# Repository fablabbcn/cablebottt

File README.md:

# CABLEBOTTT

**A hands-on STEAM workshop by FLU @ Fab Lab Barcelona.**

Design, fabricate and program a **cable-driven robot** (cablebot). Participants build a small robot that travels along a cable using a rotating motor, and bring it to life by wiring up inputs (light, distance) and outputs (motor, LED, buzzer, servo). The activity combines **mechanics + digital fabrication + computational thinking** in an accessible, creative format.

> Based on a yellow gearmotor driven from a **Seeed Studio XIAO ESP32-C3**, on a custom PCB.

---

## What you'll build

The cablebot comes in **two behaviors**, using the same hardware:

| | **Sketch A — autonomous** | **Sketch B — teleoperated** |
|---|---|---|
| **Idea** | The robot decides for itself | You drive it from your phone |
| **How** | Follows light using 2 LDR sensors | Serves a webapp over its own WiFi |
| **Inputs** | 2 light sensors (LDR) | Distance sensor (optional) |
| **Outputs** | Motor | Motor, color LED, buzzer, servo |
| **Libraries** | None | Adafruit NeoPixel + VL53L1X |
| **Best for** | Seeing a closed feedback loop | Programming your own behaviors |

Both are fully documented — see **[Programming](#3-programming)** below.

---

## Folder structure

```
cablebottt/
├── README.md                        ← you are here (project index)
│
├── fabrication/                     ← everything you cut / print / mill
│   ├── ⟨laser_pieces.svg⟩           ← laser-cut structure (the 3 assembly pieces)
│   ├── ⟨mount_3d.stl⟩               ← 3D-printed parts (if any)
│   ├── pcb/                         ← custom PCB (KiCad project + Gerbers)
│   │   ├── fab26_cablebot.kicad_pro
│   │   ├── fab26_cablebot.kicad_sch
│   │   ├── fab26_cablebot.kicad_pcb
│   │   ├── gerber/                  ← ready-to-mill / ready-to-order
│   │   └── svg/fab26_cablebot-preview.svg
│   └── silkscreen/back_silkscreen.svg
│
├── code/
│   ├── cablebottt_laser/cablebottt.ino        ← Sketch A (autonomous)
│   └── cablebottt_web/cablebottt_web.ino      ← Sketch B (teleoperated)
│
├── docs/
│   ├── cablebottt_sketch_A_tutorial.md        ← how to program Sketch A
│   └── cablebottt_sketch_B_tutorial.md        ← how to program Sketch B
│
└── images/                          ← photos & reference
    ├── ⟨assembled_bot.jpg⟩
    ├── ⟨soldering_xiao.jpg⟩
    └── ⟨pcb_render.png⟩
```

> **⟨…⟩ = placeholder.** Replace with your real filenames. If the layout above doesn't match how you organized the folder, adjust the paths — the section links below still work as long as the two `docs/…` tutorials keep their names.

---

## How to use this project

Do it in three stages. Each stage has its own detailed doc; this index just tells you the order.

### 1. Fabricate

| Part | File | Process |
|---|---|---|
| Structure | `fabrication/⟨laser_pieces.svg⟩` | Laser-cut, then assemble the 3 pieces |
| Custom PCB | `fabrication/pcb/gerber/` | Mill or order from the Gerbers |
| Board | Seeed Studio **XIAO ESP32-C3** | Solder the header pins onto the PCB |

Populate the PCB, solder the XIAO, attach the motor and the laser pointer, and assemble the laser-cut structure. Photos in **`images/`**.

### 2. Wire it up

The XIAO pinout, shared across both sketches:

| Function | Pin | Used by |
|---|---|---|
| Motor driver 1 / 2 | `D9` / `D10` | both |
| LDR left / right | `A1` / `A0` | Sketch A |
| NeoPixel (LED) | `D7` | Sketch B |
| Buzzer | `D6` | Sketch B |
| Servo | `D8` | Sketch B |
| Distance sensor SDA / SCL | `D4` / `D5` | Sketch B |

### 3. Programming

Pick the behavior and follow its step-by-step tutorial:

- **Autonomous (follows light)** → **[`docs/cablebottt_sketch_A_tutorial.md`](docs/cablebottt_sketch_A_tutorial.md)**
  *No libraries needed. Upload and go.*
- **Teleoperated (phone webapp)** → **[`docs/cablebottt_sketch_B_tutorial.md`](docs/cablebottt_sketch_B_tutorial.md)**
  *Install 2 libraries, then connect your phone to the `CABLEBOTTT` WiFi network.*

Both tutorials cover the one-time Arduino IDE + ESP32-C3 setup, so you only need to read it once.

---

## Quick start (already fabricated & flashed?)

1. Power the board over USB-C or the 9V battery.
2. **Sketch A:** shine a light near an LDR — the robot follows it.
3. **Sketch B:** on your phone, join WiFi **`CABLEBOTTT`** (password `cablebottt`), open **`http://192.168.4.1`**, and drive it.

---

*Originally created for a **FAB26 Boston** workshop. Repo: `github.com/fablabbcn/cablebottt`.*

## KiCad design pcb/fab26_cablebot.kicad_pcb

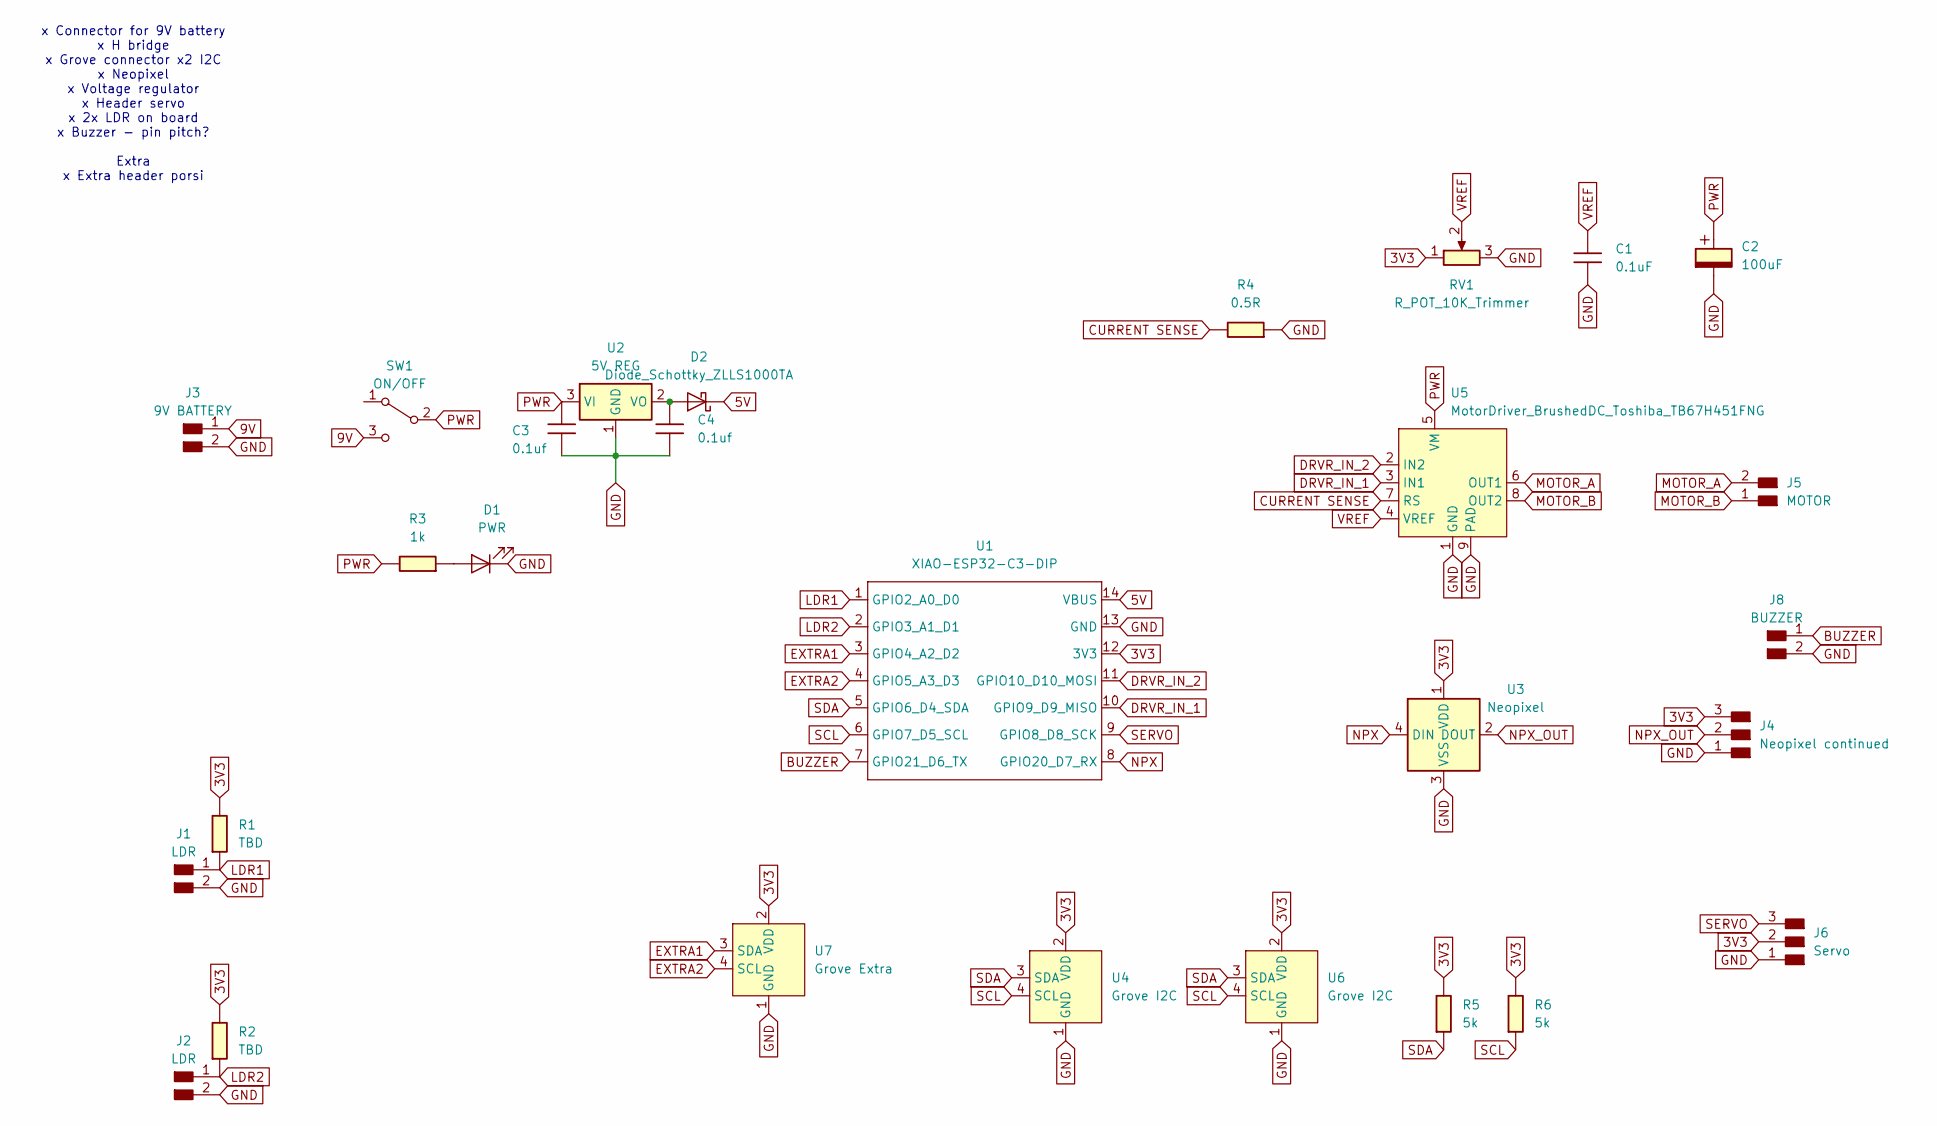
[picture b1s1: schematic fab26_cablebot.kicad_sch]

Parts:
C1: 0.1uF; C_1206
C2: 100uF; CP_Elec_100uF_Panasonic_EEE-FN1E101UL
C3, C4: 0.1uf; C_1206
D1: PWR; LED_1206
D2: Diode_Schottky_ZLLS1000TA; SOT-23
J1, J2: LDR; PinHeader_01x02_P2.54mm_Vertical_THT_D1mm
J3: 9V BATTERY; PinHeader_01x02_P2.54mm_Vertical_THT_D1mm
J4: Neopixel continued; PinHeader_01x03_P2.54mm_Vertical_THT_D1mm
J5: MOTOR; PinHeader_01x02_P2.54mm_Vertical_THT_D1mm
J6: Servo; PinHeader_01x03_P2.54mm_Vertical_THT_D1mm
J8: BUZZER; PinHeader_01x02_P2.54mm_Vertical_THT_D1mm
R1, R2: TBD; R_1206
R3: 1k; R_1206
R4: 0.5R; R_1206
R5, R6: 5k; R_1206
RV1: R_POT_10K_Trimmer; Potentiometer_TT_Model-23_4.5x5.0x3.0mm
SW1: ON/OFF; Switch_Slide_RightAngle_CnK_AYZ0102AGRLC_7.2x3mm
U1: XIAO-ESP32-C3-DIP
U2: 5V REG; SOT-223-3_TabPin2
U3: Neopixel; LED_ADDR_Worldsemi_WS2812B
U4, U6: Grove I2C; GROVE-HW4-2.0-90D
U5: MotorDriver_BrushedDC_Toshiba_TB67H451FNG; HSOP-8
U7: Grove Extra; GROVE-HW4-2.0-90D

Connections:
3V3: J4.3, J6.2, R1.1, R2.1, R5.1, R6.1, RV1.1, U1.12 (3V3), U3.1 (VDD), U4.2 (VDD), U6.2 (VDD), U7.2 (VDD)
5V: D2.3 (K), U1.14 (VBUS)
9V: J3.1, SW1.3 (C)
BUZZER: J8.1, U1.7 (GPIO21_D6_TX)
CURRENT SENSE: R4.1, U5.7 (RS)
DRVR_IN_1: U1.10 (GPIO9_D9_MISO), U5.3 (IN1)
DRVR_IN_2: U1.11 (GPIO10_D10_MOSI), U5.2 (IN2)
EXTRA1: U1.3 (GPIO4_A2_D2), U7.3 (SDA)
EXTRA2: U1.4 (GPIO5_A3_D3), U7.4 (SCL)
GND: C1.2, C2.2, C3.2, C4.2, D1.1 (K), J1.2, J2.2, J3.2, J4.1, J6.1, J8.2, R4.2, RV1.3, U1.13 (GND), U2.1 (GND), U3.3 (VSS), U4.1 (GND), U5.1 (GND), U5.9 (PAD), U6.1 (GND), U7.1 (GND)
LDR1: J1.1, R1.2, U1.1 (GPIO2_A0_D0)
LDR2: J2.1, R2.2, U1.2 (GPIO3_A1_D1)
MOTOR_A: J5.2, U5.6 (OUT1)
MOTOR_B: J5.1, U5.8 (OUT2)
NPX: U1.8 (GPIO20_D7_RX), U3.4 (DIN)
NPX_OUT: J4.2, U3.2 (DOUT)
unnamed: D1.2 (A), R3.2
unnamed: C4.1, D2.1 (A), U2.2 (VO)
PWR: C2.1, C3.1, R3.1, SW1.2 (B), U2.3 (VI), U5.5 (VM)
SCL: R6.2, U1.6 (GPIO7_D5_SCL), U4.4 (SCL), U6.4 (SCL)
SDA: R5.2, U1.5 (GPIO6_D4_SDA), U4.3 (SDA), U6.3 (SDA)
SERVO: J6.3, U1.9 (GPIO8_D8_SCK)
VREF: C1.1, RV1.2, U5.4 (VREF)

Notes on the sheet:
x Connector for 9V battery x H bridge x Grove connector x2 I2C x Neopixel x Voltage regulator x Header servo x 2x LDR on board x Buzzer - pin pitch? Extra x Extra header porsi

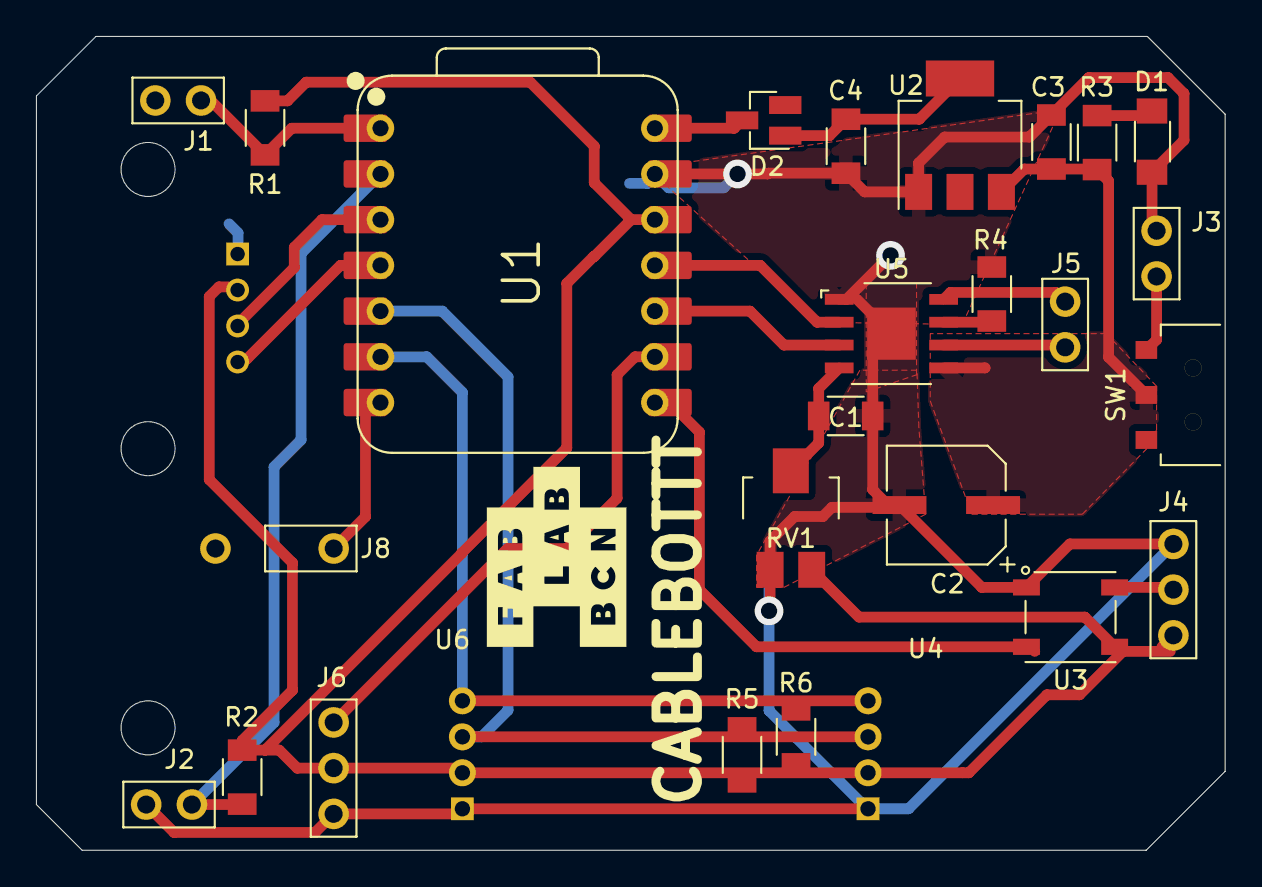
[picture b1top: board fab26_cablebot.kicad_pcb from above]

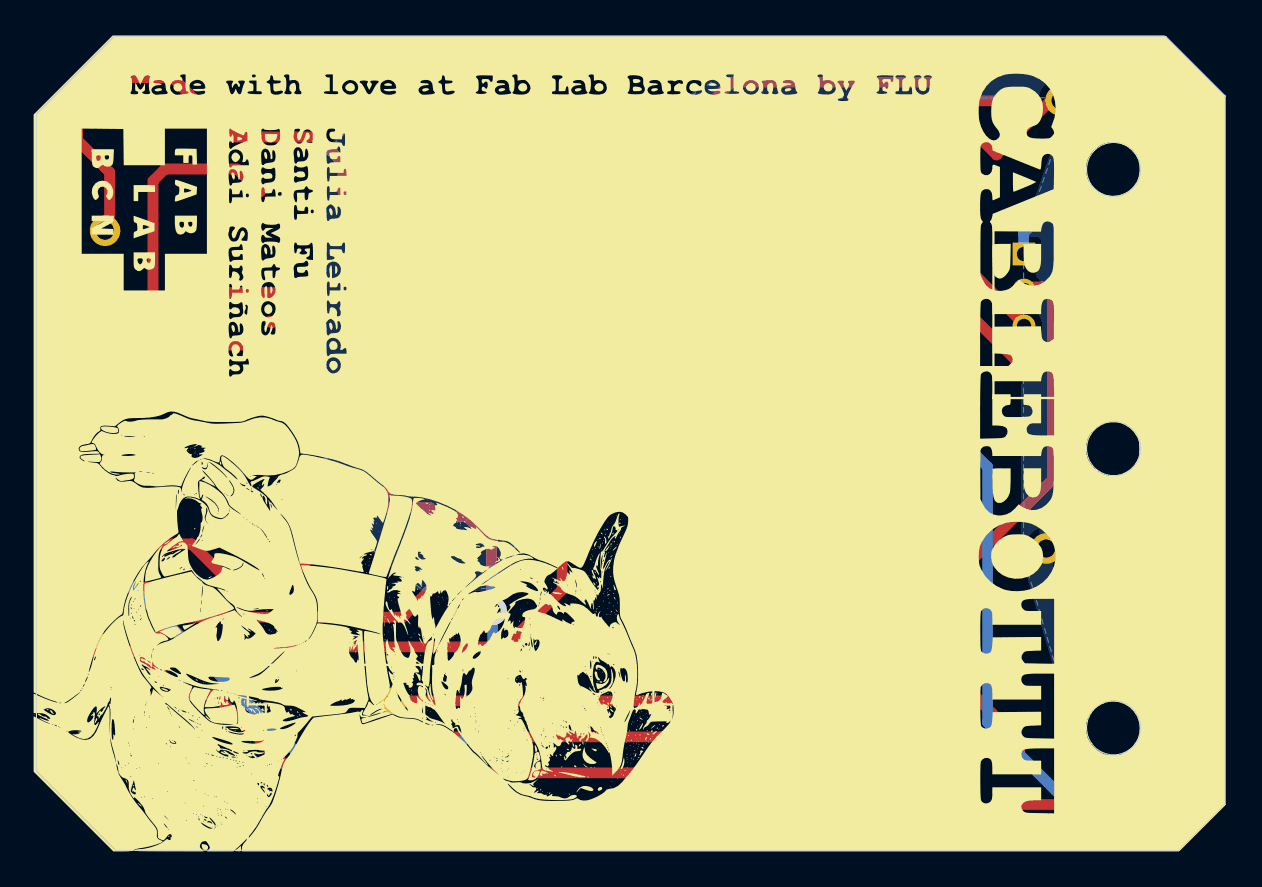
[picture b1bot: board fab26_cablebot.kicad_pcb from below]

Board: 2 copper layers, 66.0 x 45.2 mm, 28 parts (3 on the bottom side), 23 nets.

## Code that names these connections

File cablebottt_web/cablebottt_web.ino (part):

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#include <Adafruit_NeoPixel.h>
#include <Adafruit_VL53L1X.h>

#define LDR1_PIN D0
#define LDR2_PIN D1
#define NEOPIXEL_PIN D7
#define MOTOR_PIN1 D10
#define MOTOR_PIN2 D9
#define BUZZER_PIN D6
#define I2C_SDA_PIN D4
#define I2C_SCL_PIN D5
#define SERVO_PIN D8

#define NUM_PIXELS 1
#define MOTOR_STRENGTH 200
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
<div class="card">
  <div class="servo-header">
    <p class="label" style="margin:0">Servo</p>
    <span id="servoOut">90 grados</span>
  </div>
  <input type="range" min="0" max="180" step="1" value="90" id="servoSlider">
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}

void servoSetup() {
  pwmAttach(SERVO_PIN, SERVO_FREQ, SERVO_RES_BITS, SERVO_LEDC_CH);
}

void servoWriteAngle(int angle) {
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  uint32_t us = map(angle, 0, 180, SERVO_MIN_US, SERVO_MAX_US);
  uint32_t maxCount = (1UL << SERVO_RES_BITS);
  uint32_t duty = (uint32_t)(((uint64_t)us * maxCount) / SERVO_PERIOD_US);
  pwmWrite(SERVO_PIN, SERVO_LEDC_CH, duty);
}

void setMotor(int dir, int strength) {
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  marioNoteStart = millis();
  int freq = marioTune[idx].freq;
  if (freq > 0) {
    tone(BUZZER_PIN, freq);
  } else {
    noTone(BUZZER_PIN);
  }
}

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  if (millis() - marioNoteStart >= (unsigned long)marioTune[marioIndex].dur) {
    int next = marioIndex + 1;
    if (next >= MARIO_TUNE_LENGTH) {
      noTone(BUZZER_PIN);
      marioIndex = -1;
    } else {
      startMarioNote(next);
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
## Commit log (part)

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2026-06-30 Initial commit with LDR analog reading smoothing
2026-06-30 Working motor control
